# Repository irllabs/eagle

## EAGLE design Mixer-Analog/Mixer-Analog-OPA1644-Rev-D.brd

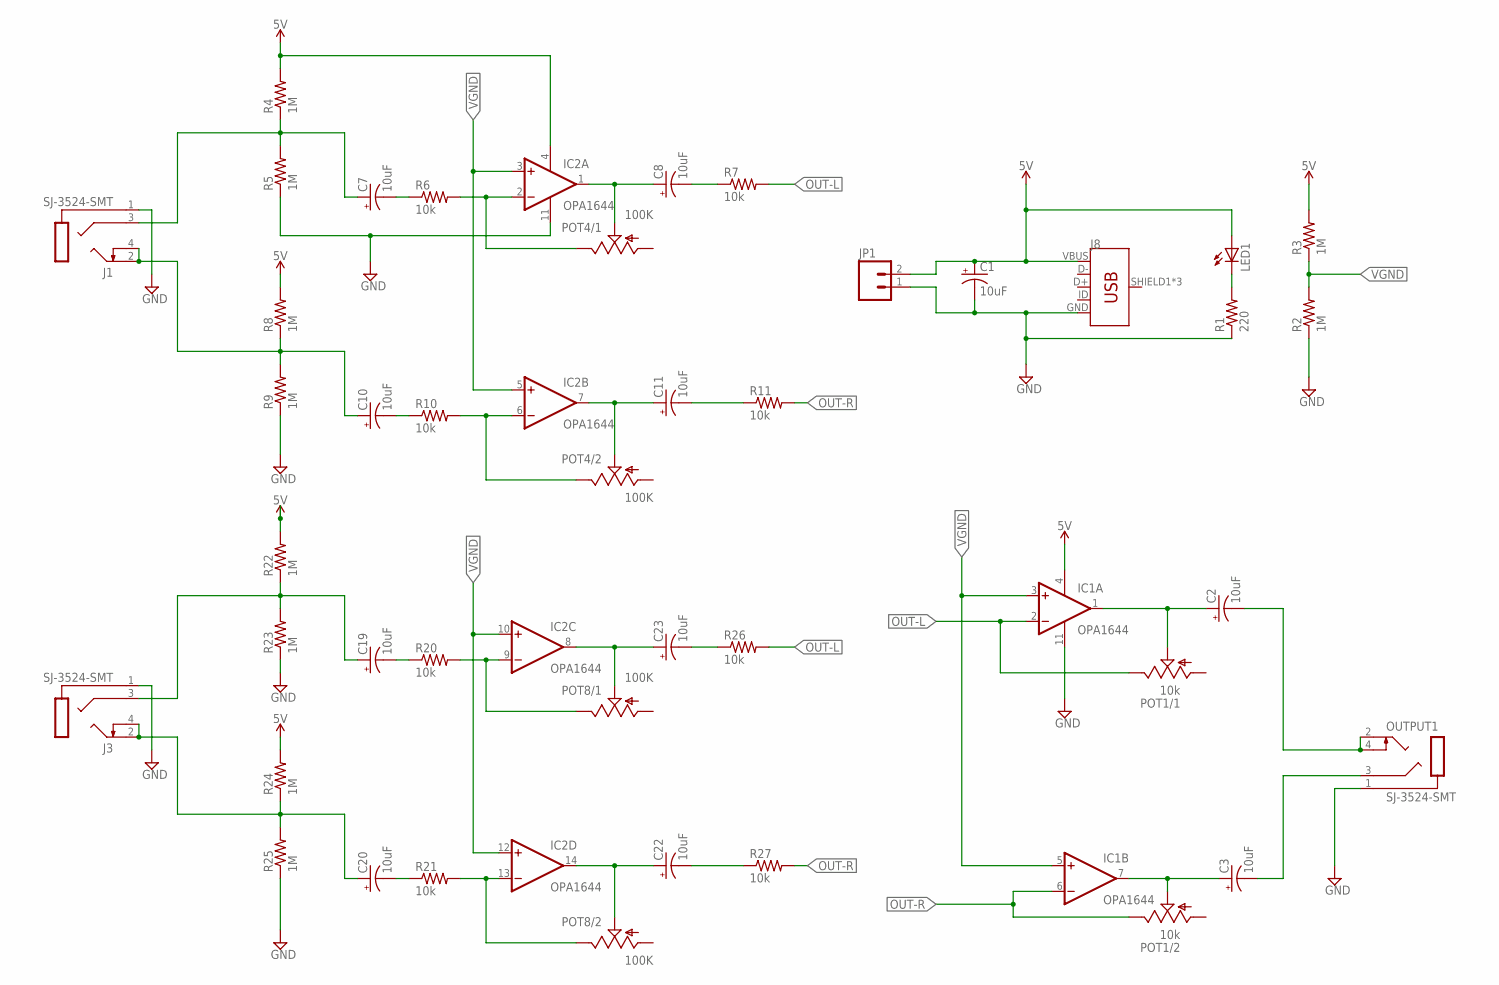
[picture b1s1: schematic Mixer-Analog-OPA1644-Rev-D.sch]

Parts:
C1, C2, C3, C7, C8, C10, C11, C19, C20, C22, C23: 10uF; EIA3216-KIT
IC1, IC2: OPA1644; TSSOP14
J1, J3: SJ-3524-SMT
J8: USB_MICRO-B_FEMALE-SMT; USB-B-MICRO-SMD
JP1: M02LOCK; 1X02_LOCK
LED1: LED3MM
OUTPUT1: SJ-3524-SMT
POT1: 10k; PTV112
POT4, POT8: 100K; PTV112
R1: 220; 0603-RES
R2, R3, R4, R5, R8, R9, R22, R23, R24, R25: 1M; 0603-RES
R6, R7, R10, R11, R20, R21, R26, R27: 10k; 0603-RES

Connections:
5V: C1.A (+), IC1.4 (V+), IC2.4 (V+), J8.VBUS, JP1.2, LED1.A, R3.2, R4.2, R8.2, R24.2
DLE: C8.A (+), IC2.1 (OUT), POT4.1.2 (S)
DLE2: C23.A (+), IC2.8 (OUT), POT8.1.2 (S)
GND: C1.C (-), IC1.11 (V-), IC2.11 (V-), J1.1 (S), J3.1 (S), J8.GND, JP1.1, OUTPUT1.1 (S), R1.1, R2.1, R5.1, R9.1, R23.1, R25.1
unnamed: IC2.6 (-IN), POT4.2.3 (E), R10.2
unnamed: C8.C (-), R7.1
unnamed: C10.A (+), J1.2 (T), J1.4 (TS), R8.1, R9.2
unnamed: IC2.2 (-IN), POT4.1.3 (E), R6.2
unnamed: C11.C (-), R11.1
unnamed: C2.A (+), IC1.1 (OUT), POT1.1.2 (S)
unnamed: C7.C (-), R6.1
unnamed: C7.A (+), J1.3 (R), R4.1, R5.2
unnamed: C10.C (-), R10.1
unnamed: LED1.K (C), R1.2
unnamed: C3.A (+), IC1.7 (OUT), POT1.2.2 (S)
unnamed: C11.A (+), IC2.7 (OUT), POT4.2.2 (S)
unnamed: C22.A (+), IC2.14 (OUT), POT8.2.2 (S)
unnamed: IC2.13 (-IN), POT8.2.3 (E), R21.2
unnamed: C20.A (+), J3.2 (T), J3.4 (TS), R24.1, R25.2
unnamed: C19.A (+), J3.3 (R), R22.1, R23.2
unnamed: C19.C (-), R20.1
unnamed: IC2.9 (-IN), POT8.1.3 (E), R20.2
unnamed: C20.C (-), R21.1
unnamed: C23.C (-), R26.1
unnamed: C22.C (-), R27.1
unnamed: C2.C (-), OUTPUT1.2 (T), OUTPUT1.4 (TS)
unnamed: C3.C (-), OUTPUT1.3 (R)
OUT-L: IC1.2 (-IN), POT1.1.3 (E), R7.2, R26.2
OUT-R: IC1.6 (-IN), POT1.2.3 (E), R11.2, R27.2
VGND: IC1.3 (+IN), IC1.5 (+IN), IC2.3 (+IN), IC2.5 (+IN), IC2.10 (+IN), IC2.12 (+IN), R2.2, R3.1

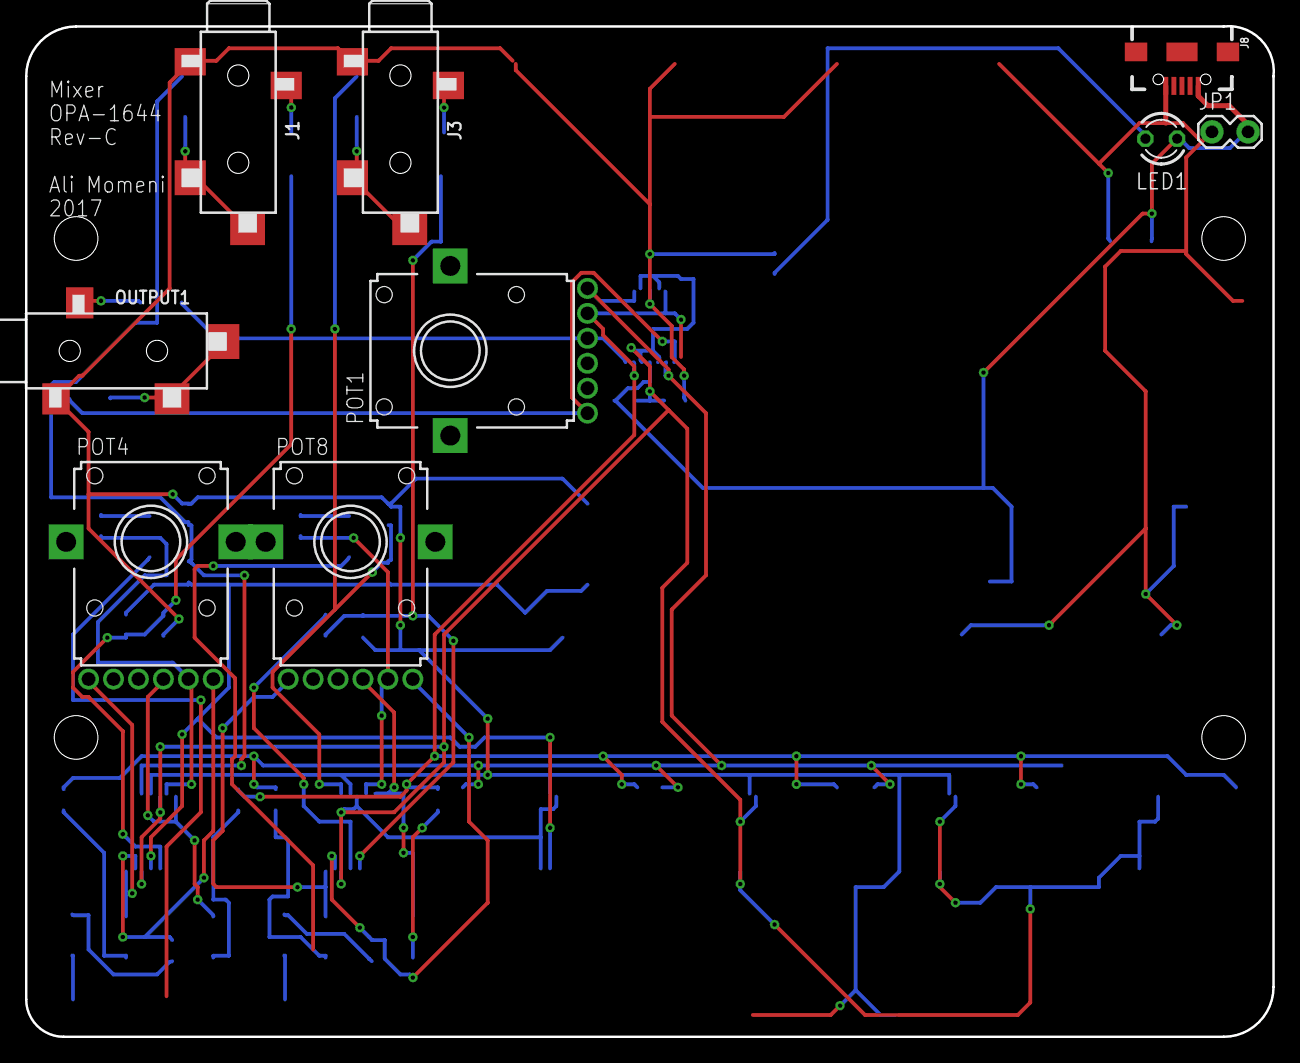
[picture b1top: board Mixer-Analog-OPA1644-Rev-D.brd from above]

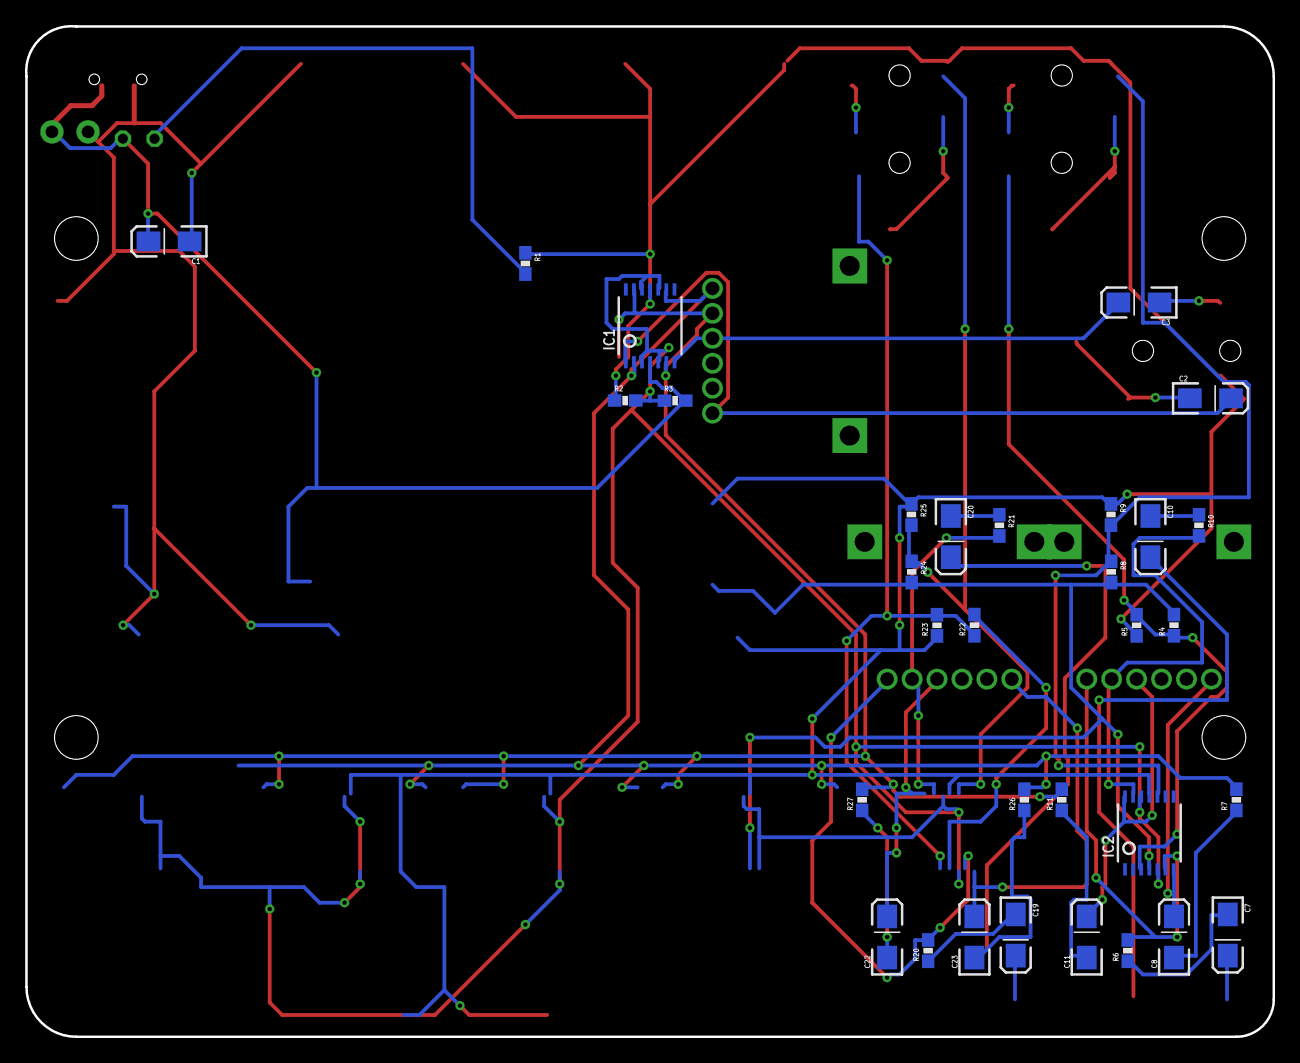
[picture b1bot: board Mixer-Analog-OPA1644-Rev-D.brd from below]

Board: 2 copper layers, 100.0 x 81.0 mm, 41 parts (32 on the bottom side), 30 nets.

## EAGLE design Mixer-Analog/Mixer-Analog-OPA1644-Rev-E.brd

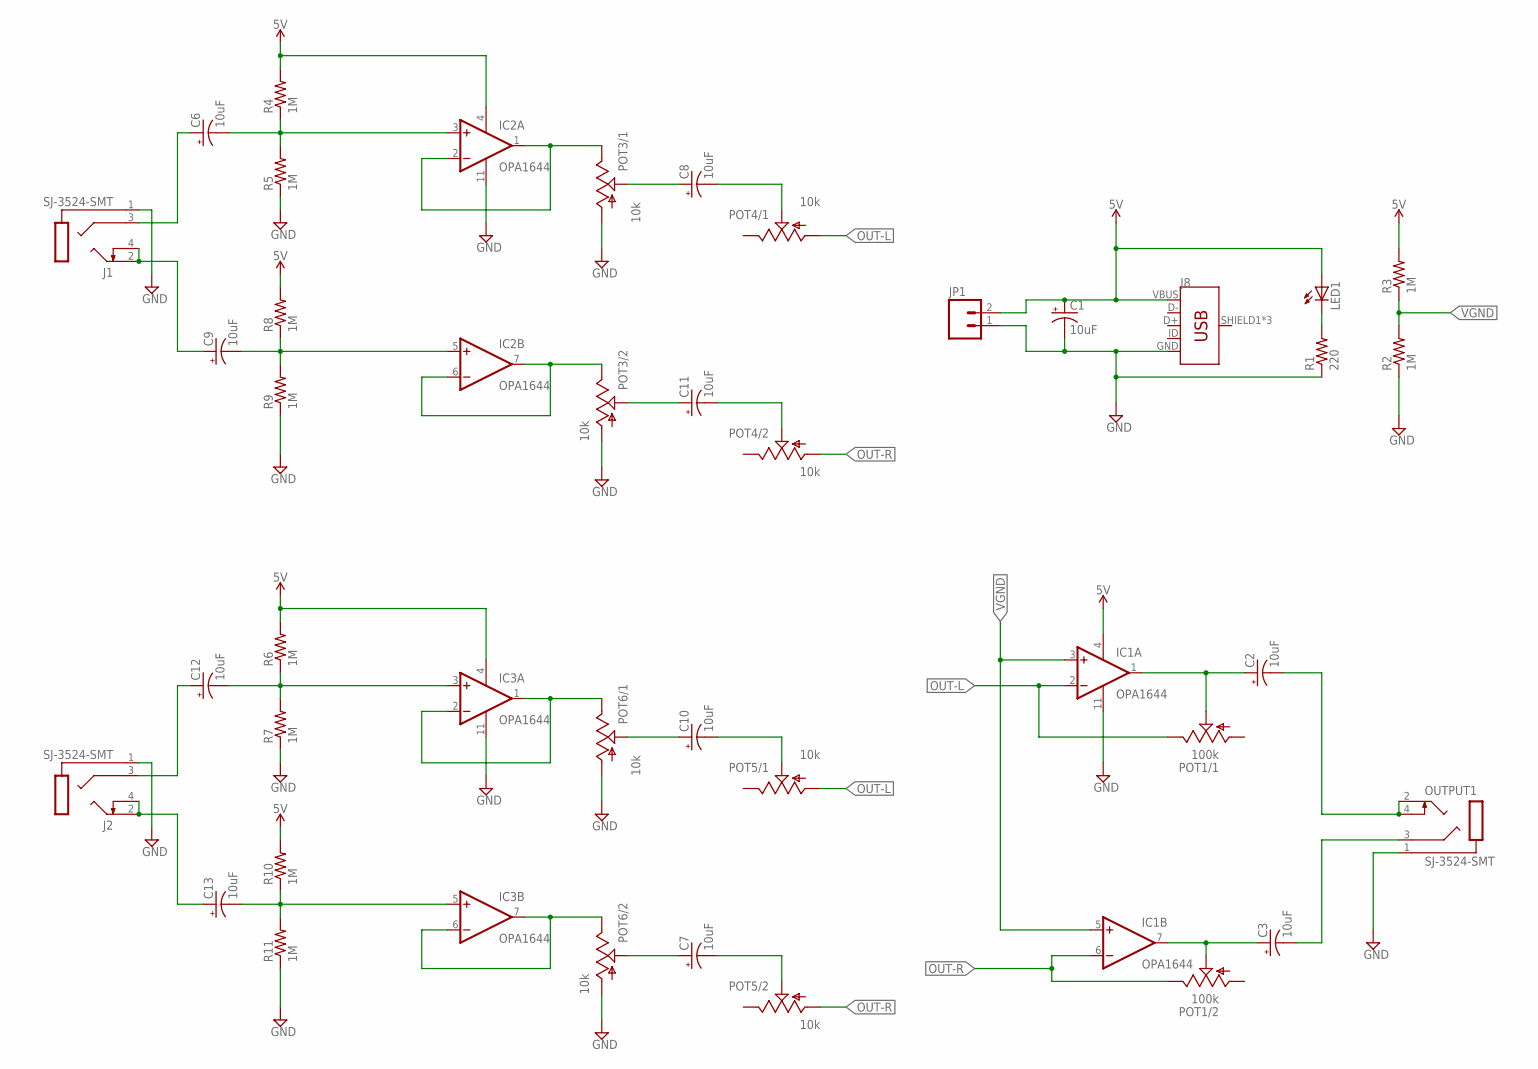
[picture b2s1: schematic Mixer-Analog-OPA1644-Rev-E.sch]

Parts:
C1, C2, C3, C6, C7, C8, C9, C10, C11, C12, C13: 10uF; EIA3216-KIT
IC1, IC2, IC3: OPA1644; TSSOP14
J1, J2: SJ-3524-SMT
J8: USB_MICRO-B_FEMALE-SMT; USB-B-MICRO-SMD
JP1: M02LOCK; 1X02_LOCK
LED1: LED3MM
OUTPUT1: SJ-3524-SMT
POT1: 100k; PTV112
POT3, POT4, POT5, POT6: 10k; PTV112
R1: 220; 0603-RES
R2, R3, R4, R5, R6, R7, R8, R9, R10, R11: 1M; 0603-RES

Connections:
5V: C1.A (+), IC1.4 (V+), IC2.4 (V+), IC3.4 (V+), J8.VBUS, JP1.2, LED1.A, R3.2, R4.2, R6.2, R8.2, R10.2
DLE: IC2.1 (OUT), IC2.2 (-IN), POT3.1.3 (E)
DLE1: IC3.1 (OUT), IC3.2 (-IN), POT6.1.3 (E)
GND: C1.C (-), IC1.11 (V-), IC2.11 (V-), IC3.11 (V-), J1.1 (S), J2.1 (S), J8.GND, JP1.1, OUTPUT1.1 (S), POT3.1.1 (A), POT3.2.1 (A), POT6.1.1 (A), POT6.2.1 (A), R1.1, R2.1, R5.1, R7.1, R9.1, R11.1
unnamed: C8.A (+), POT3.1.2 (S)
unnamed: C8.C (-), POT4.1.2 (S)
unnamed: C9.C (-), IC2.5 (+IN), R8.1, R9.2
unnamed: C11.A (+), POT3.2.2 (S)
unnamed: C6.A (+), J1.3 (R)
unnamed: C11.C (-), POT4.2.2 (S)
unnamed 10: C2.A (+), IC1.1 (OUT), POT1.1.2 (S); also elsewhere on the board
unnamed: IC3.6 (-IN), IC3.7 (OUT), POT6.2.3 (E)
unnamed: C9.A (+), J1.2 (T), J1.4 (TS)
unnamed: C10.C (-), POT5.1.2 (S)
unnamed: C7.C (-), POT5.2.2 (S)
unnamed: C13.C (-), IC3.5 (+IN), R10.1, R11.2
unnamed: C12.A (+), J2.3 (R)
unnamed: C13.A (+), J2.2 (T), J2.4 (TS)
unnamed: LED1.K (C), R1.2
unnamed: C10.A (+), POT6.1.2 (S)
unnamed 20: C3.A (+), IC1.7 (OUT), POT1.2.2 (S); also elsewhere on the board
unnamed: C7.A (+), POT6.2.2 (S)
unnamed: IC2.6 (-IN), IC2.7 (OUT), POT3.2.3 (E)
unnamed: C2.C (-), OUTPUT1.2 (T), OUTPUT1.4 (TS)
unnamed: C3.C (-), OUTPUT1.3 (R)
OUT-L: IC1.2 (-IN), POT1.1.3 (E), POT4.1.1 (A), POT5.1.1 (A); also elsewhere on the board
OUT-R: IC1.6 (-IN), POT1.2.3 (E), POT4.2.1 (A), POT5.2.1 (A); also elsewhere on the board
VGND: C6.C (-), IC1.3 (+IN), IC1.5 (+IN), IC2.3 (+IN), R2.2, R3.1, R4.1, R5.2
VGND1: C12.C (-), IC3.3 (+IN), R6.1, R7.2

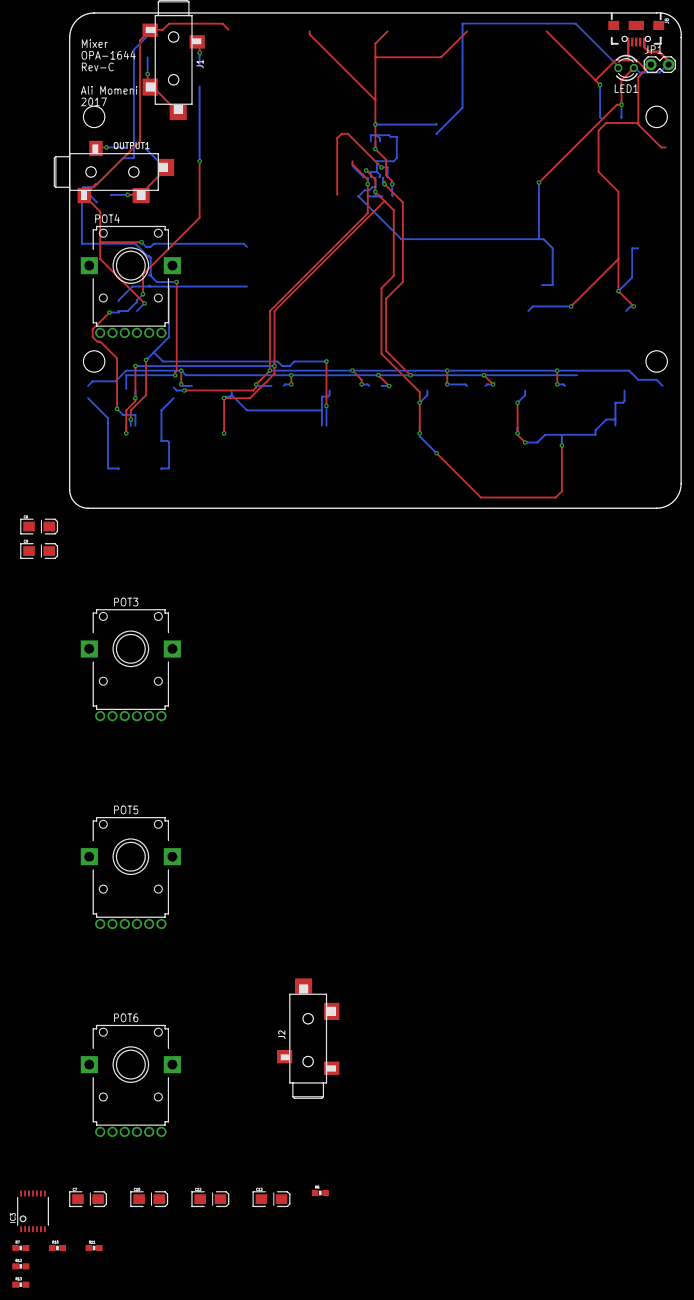
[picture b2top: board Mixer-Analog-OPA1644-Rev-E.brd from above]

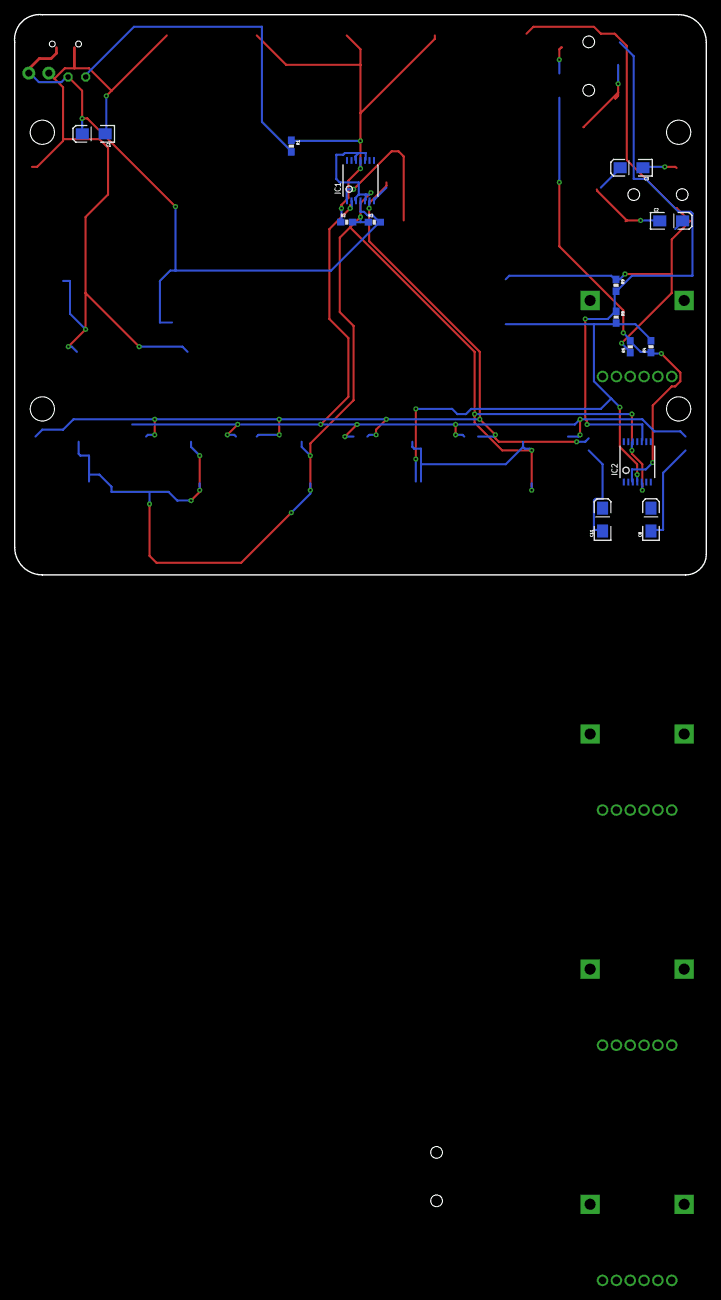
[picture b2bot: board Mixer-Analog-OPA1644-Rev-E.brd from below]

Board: 2 copper layers, 100.0 x 81.0 mm, 37 parts (14 on the bottom side), 29 nets.

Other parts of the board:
R12, R13: 100K; 0603-RES

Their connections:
unnamed 10: R12.2; also elsewhere on the board
unnamed 20: R13.2; also elsewhere on the board
OUT-L: R12.1; also elsewhere on the board
OUT-R: R13.1; also elsewhere on the board

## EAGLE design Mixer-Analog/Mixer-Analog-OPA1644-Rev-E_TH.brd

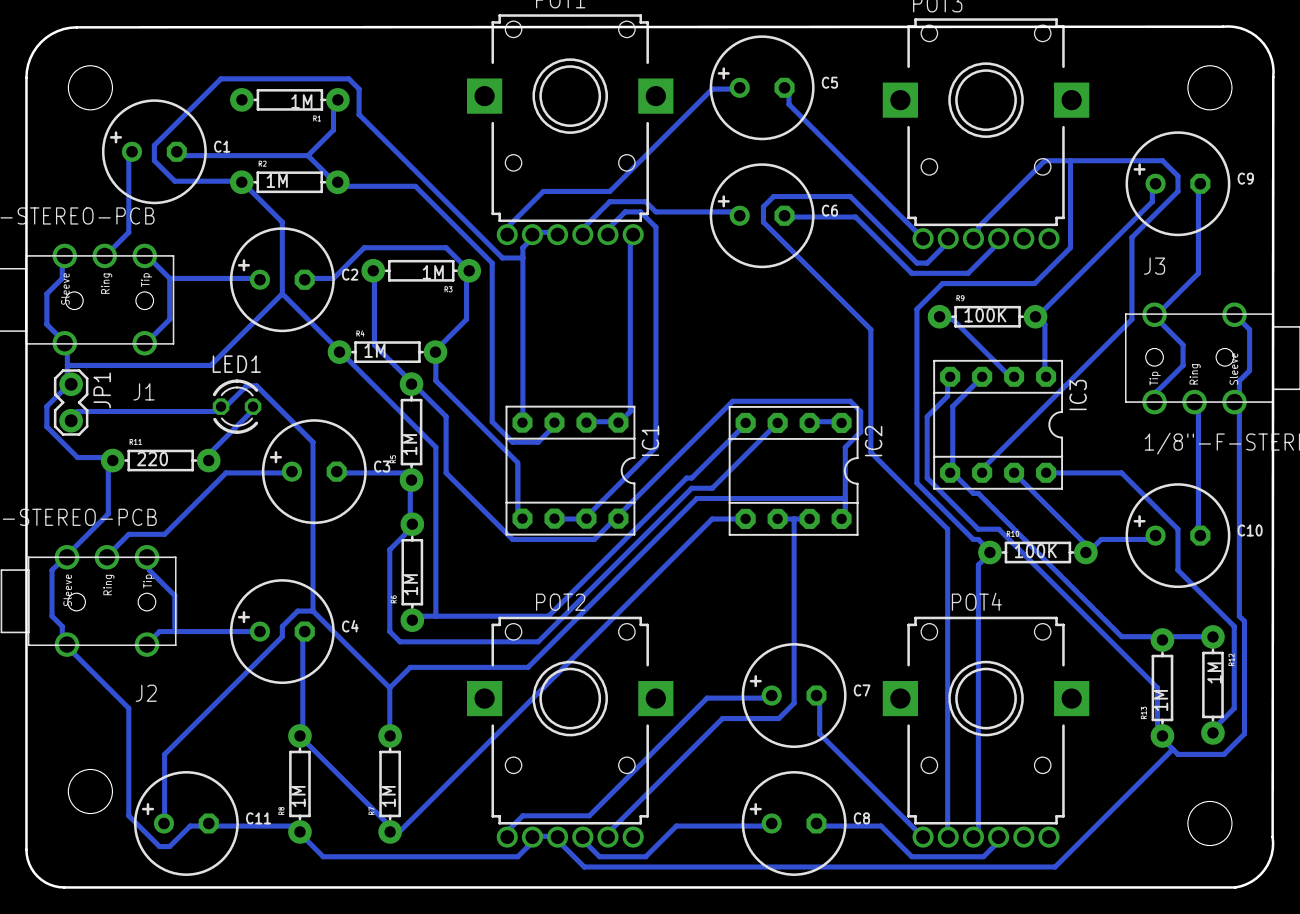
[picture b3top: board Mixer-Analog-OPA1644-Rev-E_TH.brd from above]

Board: 2 copper layers, 99.0 x 68.4 mm, 36 parts (0 on the bottom side), 30 nets.

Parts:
C1, C2, C3, C4, C5, C6, C7, C8, C9, C10, C11: 10uFV; CELEC_3.5MM_8MM
IC1, IC2, IC3: OPA2134P; DIL08
J1, J2, J3: 1/8"-F-STEREO-PCB
JP1: 1X02_LOCK
LED1: LED3MM
POT1, POT2, POT3: 10k; PTV112
POT4: 100k; PTV112
R1, R3, R4, R5, R6, R7, R8, R12, R13: 1M; AXIAL-0.3EZ
R2: 1M; AXIAL-0.3
R9, R10: 100K; AXIAL-0.3EZ
R11: 220; AXIAL-0.3EZ

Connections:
5V: C11.+, IC1.8, IC2.8, IC3.8, JP1.2, LED1.A, R1.P$2, R3.P$2, R5.P$2, R7.P$2, R12.P$2
DLE: IC1.1, IC1.2, POT1.1.3
GND: C11.-, IC1.4, IC2.4, IC3.4, J1.SLEEVE1, J1.SLEEVE2, J2.SLEEVE1, J2.SLEEVE2, J3.SLEEVE1, J3.SLEEVE2, JP1.1, POT1.1.1, POT1.2.1, POT2.1.1, POT2.2.1, R2.P$1, R4.P$1, R6.P$1, R8.P$1, R11.P$1, R13.P$1
unnamed: C5.-, POT3.1.2
unnamed: C2.-, IC1.5, R3.P$1, R4.P$2
unnamed: C6.+, POT1.2.2
unnamed: C1.+, J1.RING
unnamed: C6.-, POT3.2.2
unnamed: C9.+, IC3.1, R9.P$2
unnamed: IC2.6, IC2.7, POT2.2.3
unnamed: C2.+, J1.TIP1, J1.TIP2
unnamed: C7.-, POT4.1.2
unnamed: C8.-, POT4.2.2
unnamed: C4.-, IC2.5, R7.P$1, R8.P$2
unnamed: C3.+, J2.RING
unnamed: C4.+, J2.TIP1, J2.TIP2
unnamed: LED1.K, R11.P$2
unnamed: C7.+, POT2.1.2
unnamed: C10.+, IC3.7, R10.P$2
unnamed: C8.+, POT2.2.2
unnamed: IC1.6, IC1.7, POT1.2.3
unnamed: IC2.1, IC2.2, POT2.1.3
unnamed: C3.-, IC2.3, R5.P$1, R6.P$2
unnamed: C1.-, IC1.3, R1.P$1, R2.P$2
unnamed: C9.-, J3.TIP1, J3.TIP2
unnamed: C10.-, J3.RING
OUT-L: IC3.2, POT3.1.1, POT4.1.1, R9.P$1
OUT-R: IC3.6, POT3.2.1, POT4.2.1, R10.P$1
POT1: C5.+, POT1.1.2
VGND: IC3.3, IC3.5, R12.P$1, R13.P$2

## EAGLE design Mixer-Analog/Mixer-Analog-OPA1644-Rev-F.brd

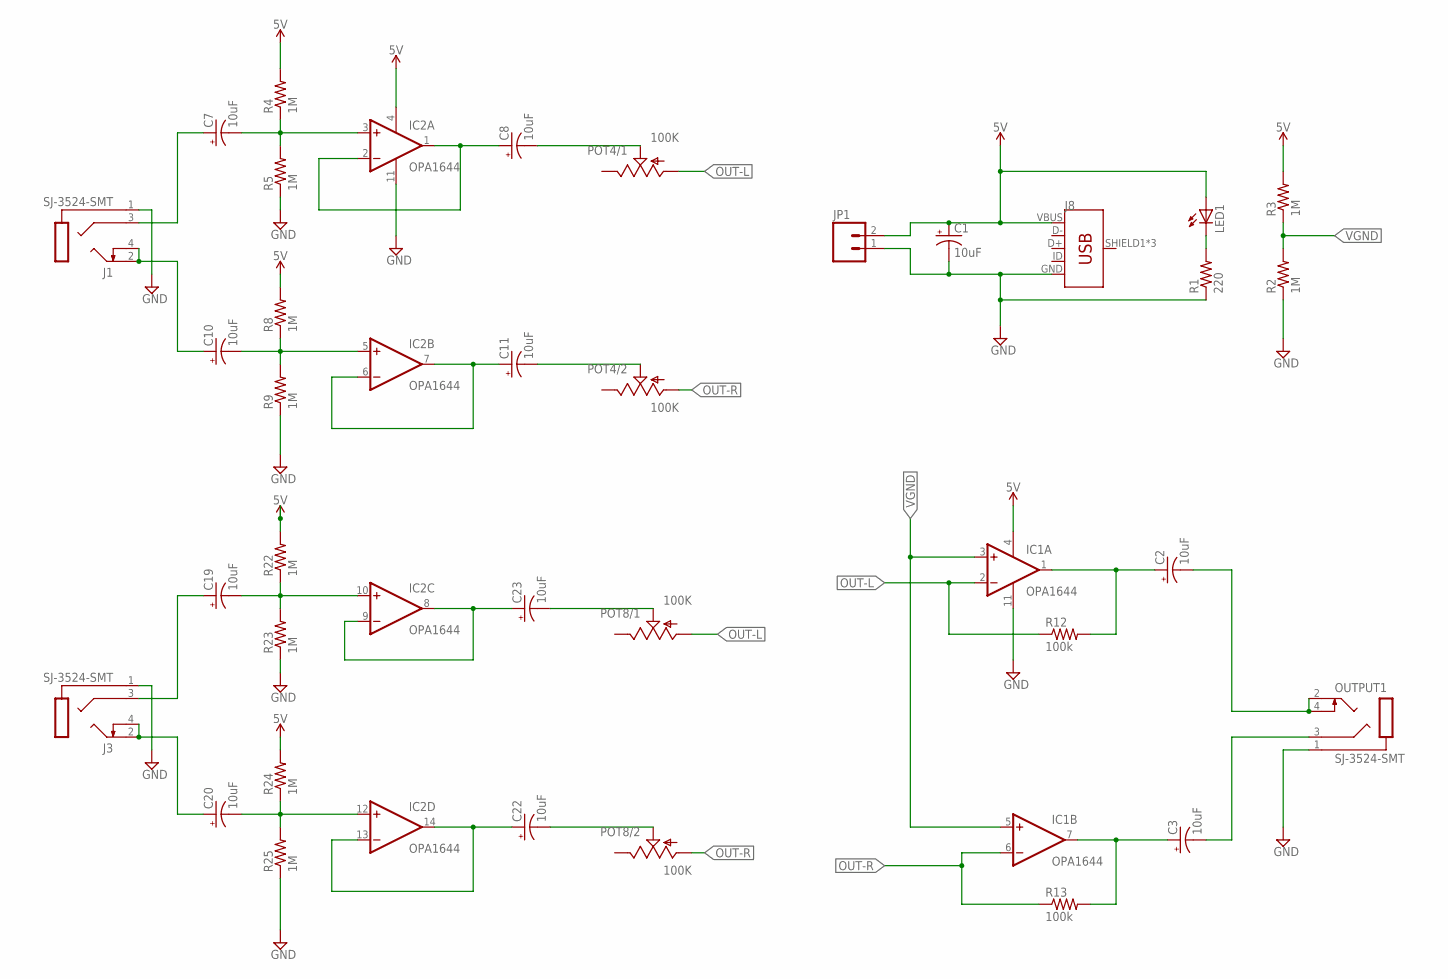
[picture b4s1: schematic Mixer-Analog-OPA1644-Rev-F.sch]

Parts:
C1, C2, C3, C7, C8, C10, C11, C19, C20, C22, C23: 10uF; EIA3216-KIT
IC1, IC2: OPA1644; TSSOP14
J1, J3: SJ-3524-SMT
J8: USB_MICRO-B_FEMALE-SMT; USB-B-MICRO-SMD
JP1: M02LOCK; 1X02_LOCK
LED1: LED3MM
OUTPUT1: SJ-3524-SMT
POT4, POT8: 100K; PTV112
R1: 220; 0603-RES
R2, R3, R4, R5, R8, R9, R22, R23, R24, R25: 1M; 0603-RES
R12, R13: 100k; 0603-RES

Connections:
5V: C1.A (+), IC1.4 (V+), IC2.4 (V+), J8.VBUS, JP1.2, LED1.A, R3.2, R4.2, R8.2, R24.2
DELJ: IC2.11 (V-)
DLE: C8.A (+), IC2.1 (OUT), IC2.2 (-IN)
DLE2: C23.A (+), IC2.8 (OUT), IC2.9 (-IN)
GND: C1.C (-), IC1.11 (V-), J1.1 (S), J3.1 (S), J8.GND, JP1.1, OUTPUT1.1 (S), R1.1, R2.1, R5.1, R9.1, R23.1, R25.1
unnamed: C8.C (-), POT4.1.2 (S)
unnamed: C10.C (-), IC2.5 (+IN), R8.1, R9.2
unnamed: C11.C (-), POT4.2.2 (S)
unnamed: C19.A (+), J3.3 (R)
unnamed: C2.A (+), IC1.1 (OUT), R12.2
unnamed: C7.C (-), IC2.3 (+IN), R4.1, R5.2
unnamed: C20.A (+), J3.2 (T), J3.4 (TS)
unnamed: C10.A (+), J1.2 (T), J1.4 (TS)
unnamed: C7.A (+), J1.3 (R)
unnamed: LED1.K (C), R1.2
unnamed: C3.A (+), IC1.7 (OUT), R13.2
unnamed: C11.A (+), IC2.6 (-IN), IC2.7 (OUT)
unnamed: C22.A (+), IC2.13 (-IN), IC2.14 (OUT)
unnamed: C19.C (-), IC2.10 (+IN), R22.1, R23.2
unnamed: C20.C (-), IC2.12 (+IN), R24.1, R25.2
unnamed: C23.C (-), POT8.1.2 (S)
unnamed: C22.C (-), POT8.2.2 (S)
unnamed: C2.C (-), OUTPUT1.2 (T), OUTPUT1.4 (TS)
unnamed: C3.C (-), OUTPUT1.3 (R)
OUT-L: IC1.2 (-IN), POT4.1.1 (A), POT8.1.1 (A), R12.1
OUT-R: IC1.6 (-IN), POT4.2.1 (A), POT8.2.1 (A), R13.1
VGND: IC1.3 (+IN), IC1.5 (+IN), R2.2, R3.1

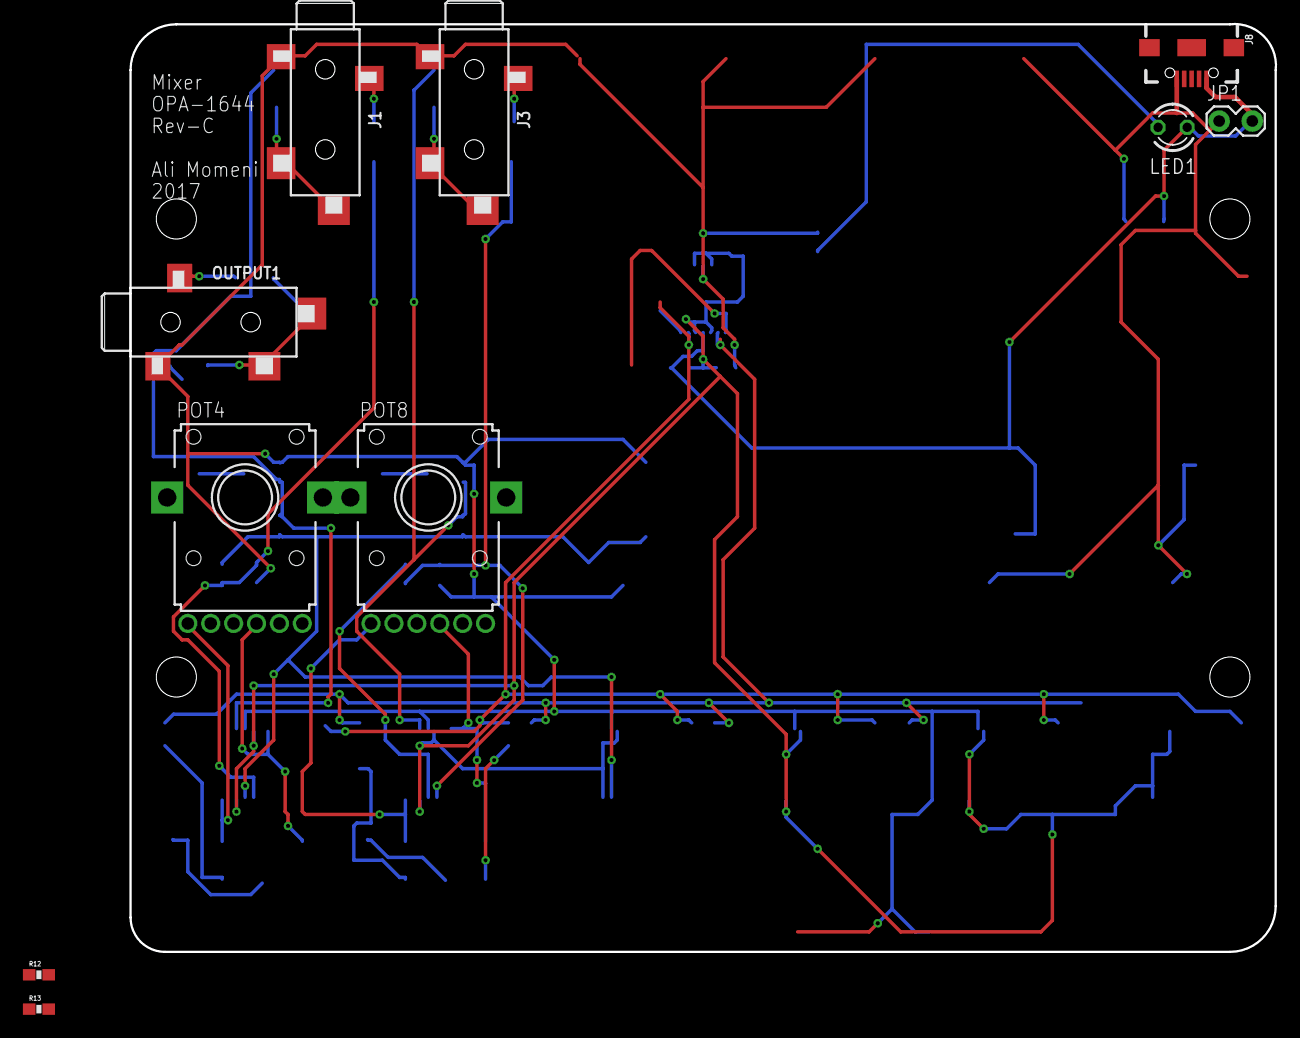
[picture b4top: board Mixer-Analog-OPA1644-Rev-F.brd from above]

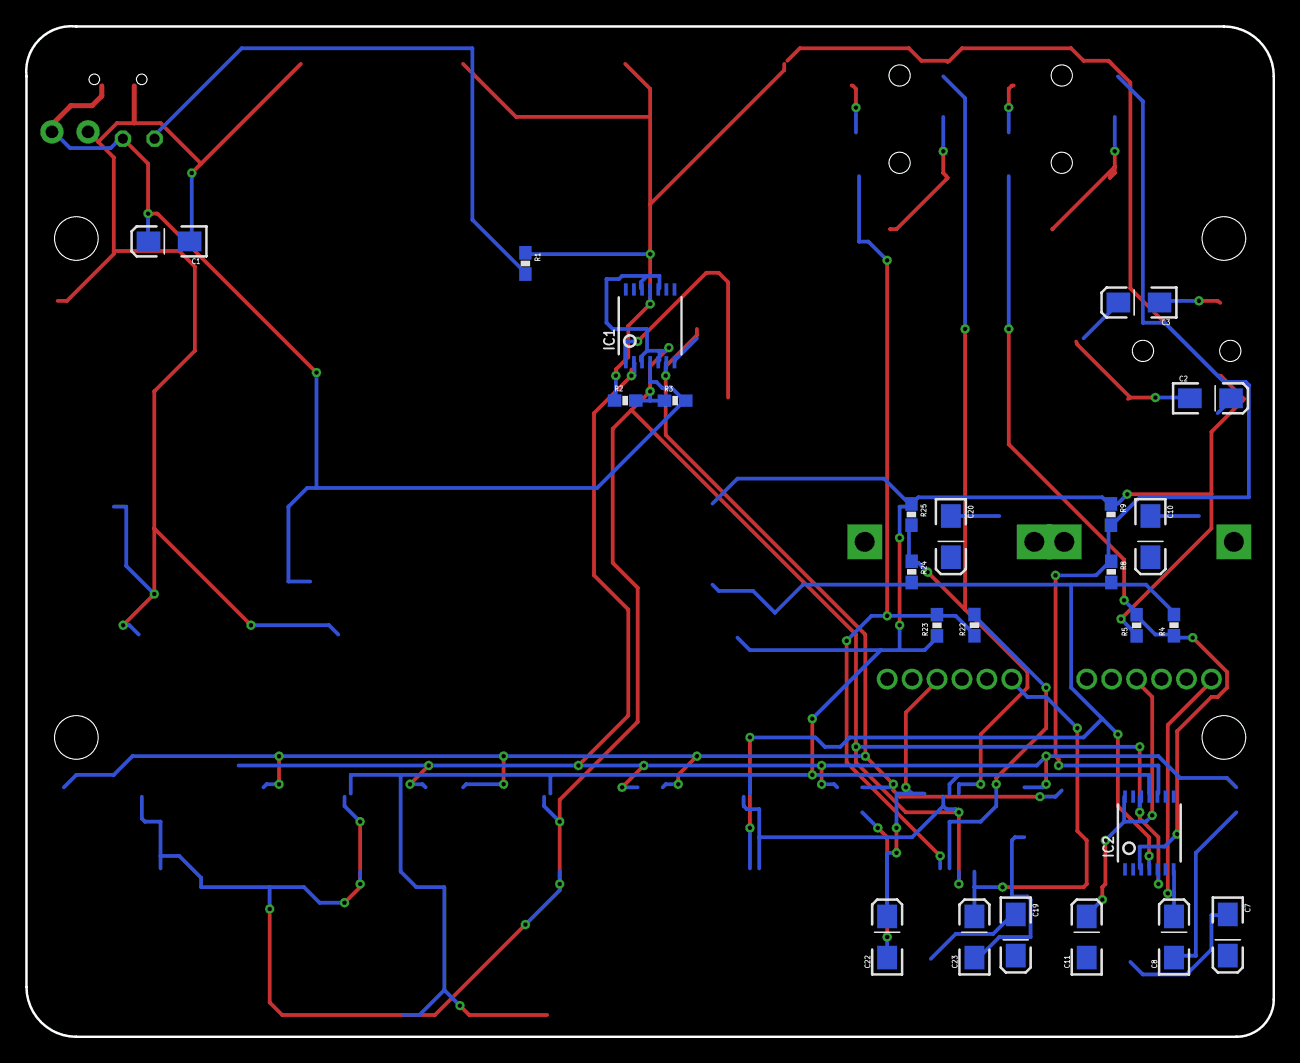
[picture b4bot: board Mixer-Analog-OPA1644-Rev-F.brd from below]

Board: 2 copper layers, 100.0 x 81.0 mm, 34 parts (24 on the bottom side), 26 nets.

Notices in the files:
parts and their libraries:
SparkFun-Passives: Licensing: Creative Commons ShareAlike 4.0 International - https://creativecommons.org/licenses/by-sa/4.0
con-cuistack: Copyright (C) 2008, Bob Starr
